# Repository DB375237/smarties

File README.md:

# Smarties™ Dispenser

Basic Arduino based dispenser. It can be activated via Bluetooth with an HC-05 module.

## How it started

## How it's going

## Warning
Some of the materials used in this project may not be food-safe. This is not meant to be an actual dispenser.

USE IT AT YOUR OWN RISK

## Licences

(generated via https://oshwa.github.io/certification-mark-generator/facts)

## Note
Smarties™ is registered trademark of Nestlé

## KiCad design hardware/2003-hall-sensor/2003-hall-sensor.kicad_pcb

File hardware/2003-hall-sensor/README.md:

# Hall Effect Sensors Board (comparators)

KiCad project of the board for the comparators for signal coming from Hall effect sensors.

It's based on the [LMV393](https://github.com/DB375237/smarties/blob/master/pdf/lmv393.pdf) low voltage comparator.

(required only for "analog" Hall sensors - not used in the prototype built - ** UNTESTED DESIGN **)

## License

Copyright © 2020-2021 DB375237 (Dario B.)

The hardware part of the Smarties™ Dispenser project is licensed under the [CERN Open Hardware Licence Version 2 - Strongly Reciprocal](https://github.com/DB375237/smarties/blob/1d4773c20f6e62bb15a9346e1278c39deedc8825/LICENSE.hardware.md)

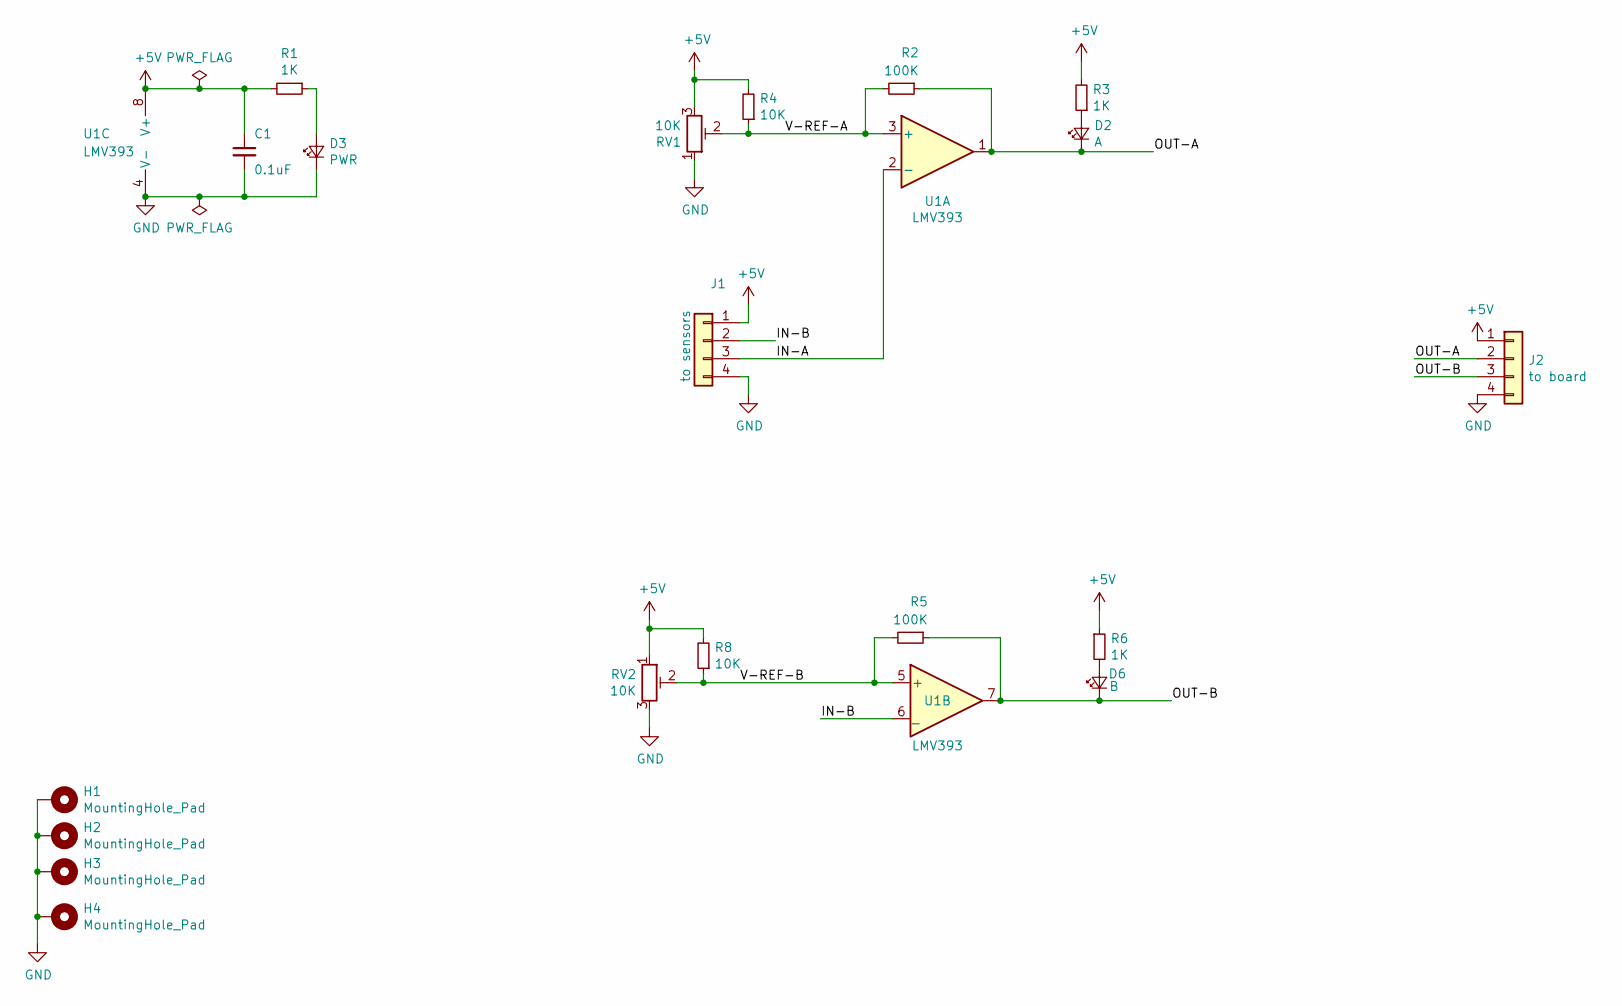
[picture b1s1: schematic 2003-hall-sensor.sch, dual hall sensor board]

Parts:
C1: 0.1uF; C_0805_2012Metric_Pad1.15x1.40mm_HandSolder
D2: A; LED_0805_2012Metric_Pad1.15x1.40mm_HandSolder
D3: PWR; LED_0805_2012Metric_Pad1.15x1.40mm_HandSolder
D6: B; LED_0805_2012Metric_Pad1.15x1.40mm_HandSolder
H1, H2, H3, H4: MountingHole_Pad; MountingHole_2.2mm_M2_Pad_Via
J1: to sensors; PinHeader_1x04_P2.54mm_Vertical
J2: to board; PinHeader_1x04_P2.54mm_Vertical
R1, R3, R6: 1K; R_0805_2012Metric_Pad1.15x1.40mm_HandSolder
R2, R5: 100K; R_0805_2012Metric_Pad1.15x1.40mm_HandSolder
R4, R8: 10K; R_0805_2012Metric_Pad1.15x1.40mm_HandSolder
RV1, RV2: 10K; Potentiometer_Vishay_TS53YL_Vertical
U1: LMV393

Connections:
+5V: C1.1, J1.1, J2.1, R1.2, R3.2, R4.2, R6.1, R8.2, RV1.3, RV2.1, U1.8 (V+)
/IN-A: J1.3, U1.2 (-)
/IN-B: J1.2, U1.6 (_)
/OUT-A: D2.1 (K), J2.2, R2.1, U1.1
/OUT-B: D6.1 (K), J2.3, R5.1, U1.7
/V-REF-A: R2.2, R4.1, RV1.2, U1.3 (+)
/V-REF-B: R5.2, R8.1, RV2.2, U1.5 (+)
GND: C1.2, D3.1 (K), H1.1, H2.1, H3.1, H4.1, J1.4, J2.4, RV1.1, RV2.3, U1.4 (V-)
unnamed: D2.2 (A), R3.1
unnamed: D3.2 (A), R1.1
unnamed: D6.2 (A), R6.2

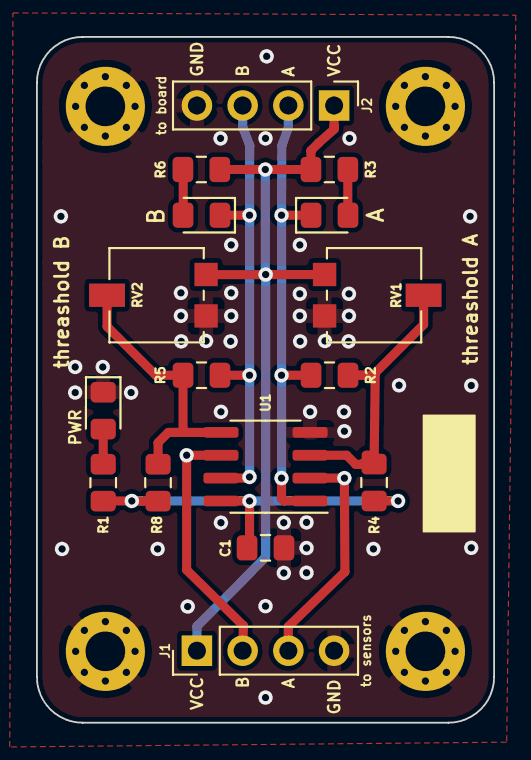
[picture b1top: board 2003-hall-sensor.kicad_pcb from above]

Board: 2 copper layers, 25.4 x 38.1 mm, 20 parts (0 on the bottom side), 11 nets.

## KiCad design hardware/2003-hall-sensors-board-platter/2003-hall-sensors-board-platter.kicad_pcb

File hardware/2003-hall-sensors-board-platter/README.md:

# Hall Effect Sensors Board (rotating platter)

KiCad project of the board for the Hall effect sensors to control the positioning of the rotating platter.

It's based on the [KY-003 sensors](https://www.amazon.it/gp/product/B07V3S94HZ).

(prototype built uses only one sensor)

## License

Copyright © 2020-2021 DB375237 (Dario B.)

The hardware part of the Smarties™ Dispenser project is licensed under the [CERN Open Hardware Licence Version 2 - Strongly Reciprocal](https://github.com/DB375237/smarties/blob/1d4773c20f6e62bb15a9346e1278c39deedc8825/LICENSE.hardware.md)

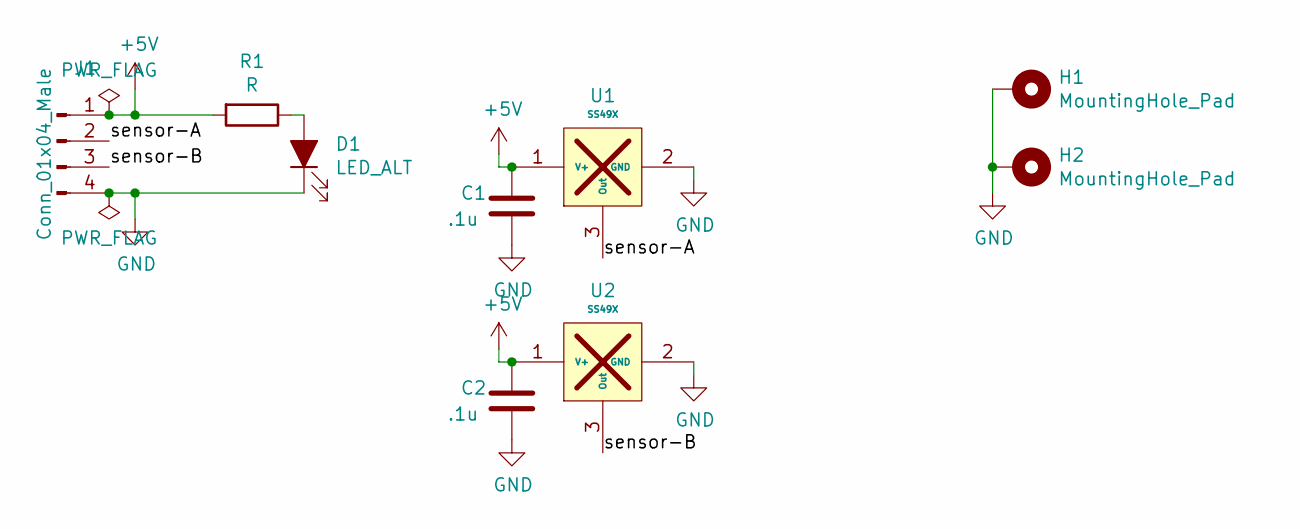
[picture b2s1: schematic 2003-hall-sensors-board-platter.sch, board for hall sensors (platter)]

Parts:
C1, C2: .1u; C_Disc_D3.0mm_W1.6mm_P2.50mm
D1: LED_ALT; LED_D3.0mm_Clear
H1, H2: MountingHole_Pad; MountingHole_3.2mm_M3_Pad_Via
J1: Conn_01x04_Male; PinHeader_1x04_P2.54mm_Vertical
R1: R; R_Axial_DIN0207_L6.3mm_D2.5mm_P10.16mm_Horizontal
U1, U2: SS49X; TO-92Flat

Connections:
+5V: C1.1, C2.1, J1.1, R1.2, U1.1 (V+), U2.1 (V+)
/sensor-A: J1.2, U1.3 (Out)
/sensor-B: J1.3, U2.3 (Out)
GND: C1.2, C2.2, D1.1 (K), H1.1, H2.1, J1.4, U1.2 (GND), U2.2 (GND)
unnamed: D1.2 (A), R1.1

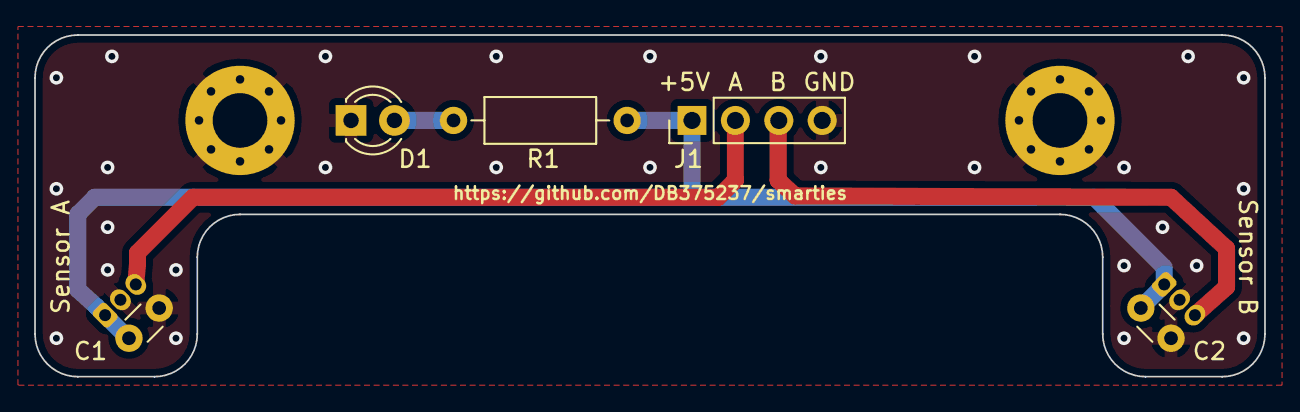
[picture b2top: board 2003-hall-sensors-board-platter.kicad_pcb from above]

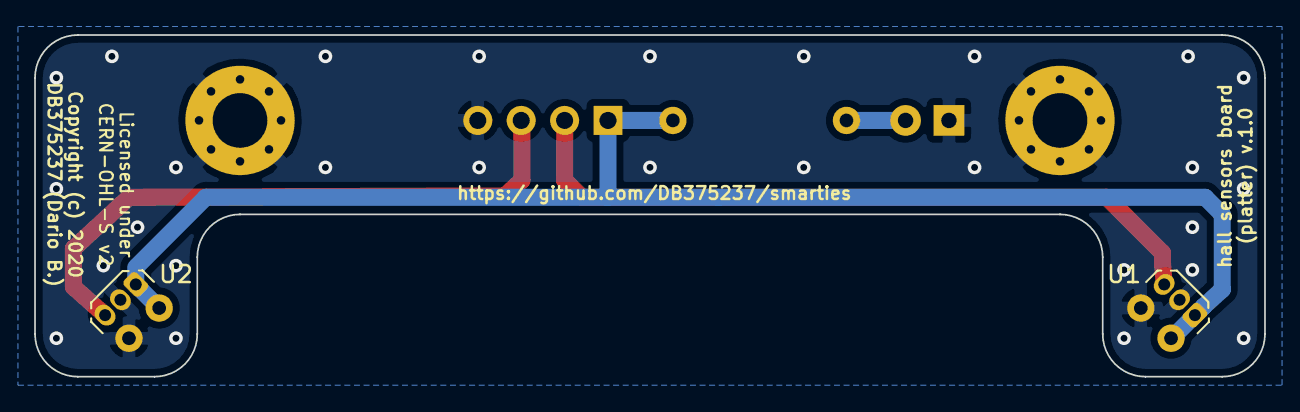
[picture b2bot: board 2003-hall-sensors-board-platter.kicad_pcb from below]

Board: 2 copper layers, 72.0 x 20.0 mm, 9 parts (2 on the bottom side), 5 nets.

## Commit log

2020-04-11 Create LICENSE
2020-04-11 added software
2020-04-11 add pdf
2020-04-13 2003-hall-sensors-board-platter
2020-04-13 added README.md
2020-04-13 added images
2020-04-13 modified README.md
2020-04-14 updated License
2020-04-17 modified README
2020-05-01 added 2003-hall-sensor
2020-05-01 added LMV393 datasheet
2020-05-09 modified LICENSE
2020-05-27 modified STL
2020-05-27 modified images
2020-11-11 add ir-barrier-01-01-FINAL.stl
2020-11-11 added ir-barrier.png
2020-11-18 added bearing-holder-1-00-02-FINAL.stl
2020-11-18 added bearing01.png
2020-11-18 modified bearing-holder-platter-01-01-Final.stl
2020-11-18 added bearing02.png
2020-11-24 added platter.png
2020-11-24 added platter-01-01-FINAL.stl
2020-11-25 added base-piatto-01-01-FINAL.stl
2020-11-25 added base_piatto.png
2021-01-30 added mdf-base-02.pdf
2021-01-30 pixel-ring-01-FINAL.stl
2021-01-30 add carousel-plate-2-01-01-FINAL.stl
2021-01-30 carousel-ring.png
2021-01-30 added pixel-ring-holder.png
2021-03-03 added dispenser project
2021-03-07 added dispenser-after.png
2021-03-07 added licenses.png
2021-03-07 CERN license
2021-03-07 added license for hardware
2021-03-07 added license for software
2021-03-07 added license for documentation
2021-03-07 removed license
2021-03-07 added Arduino test firmaware
2021-03-07 added README
2021-03-07 added bottom image
2021-03-07 added video
2021-03-07 remove license files
2021-03-07 schematic in PDF
2021-03-07 added power-board.png
2021-03-07 added gerbers

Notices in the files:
README.md:
Open Source Licenses "Facts"
hardware/2003-hall-sensor/2003-hall-sensor.kicad_pcb:
Copyright (c) 2020 DB375237 (Dario B.)
hardware/2003-hall-sensors-board-platter/2003-hall-sensors-board-platter.kicad_pcb:
CERN-OHL-S v2
